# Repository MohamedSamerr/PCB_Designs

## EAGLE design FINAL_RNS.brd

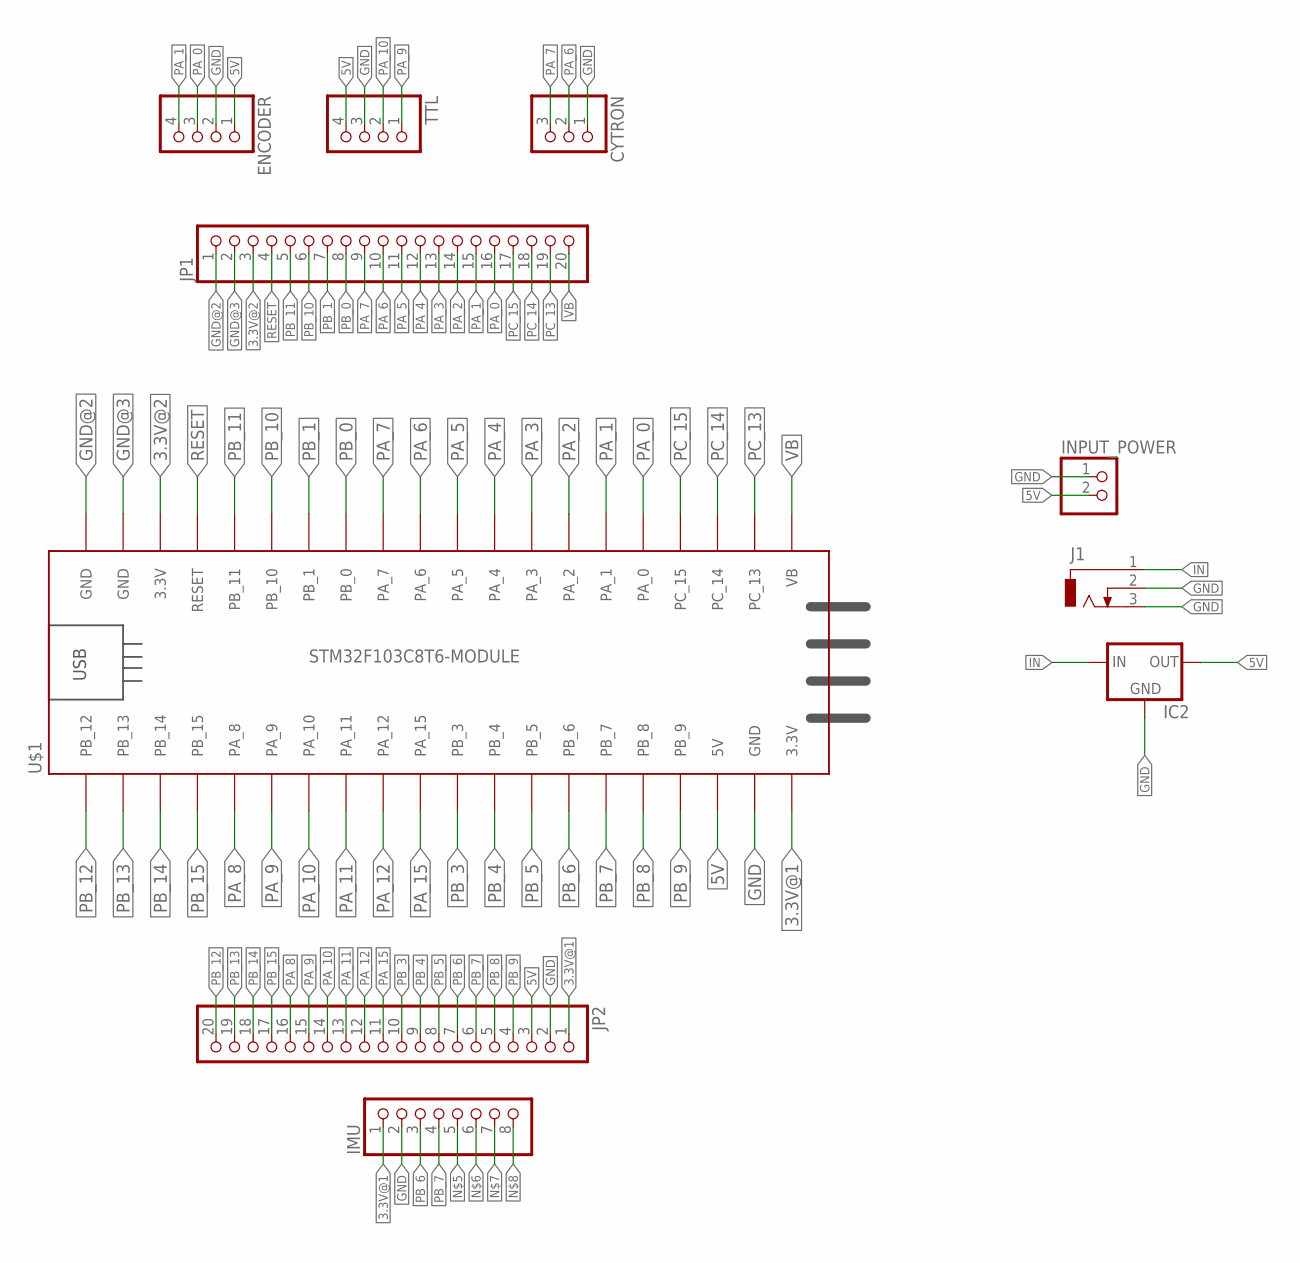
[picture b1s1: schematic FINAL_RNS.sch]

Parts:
CYTRON: PINHD-3_DATA; 1X03_DATA
ENCODER: PINHD-4_DATA; 1X04_DATA
IC2: 78XXS
IMU: PINHD-1X8; 1X08
INPUT_POWER: PINHD-2_DATA; 1X02_DATA
J1: CON_JACK; DCJ0303
JP1, JP2: PINHD-1X20; 1X20
TTL: PINHD-4_DATA; 1X04_DATA
U$1: STM32F103C8T6-MODULE

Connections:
3.3V@1: IMU.1, JP2.1, U$1.3.3V_1 (3.3V)
3.3V@2: JP1.3, U$1.3.3V_2 (3.3V)
5V: ENCODER.1, IC2.OUT, INPUT_POWER.2, JP2.3, TTL.4, U$1.5V
GND: CYTRON.1, ENCODER.2, IC2.GND, IMU.2, INPUT_POWER.1, J1.2, J1.3, JP2.2, TTL.3, U$1.GND_1 (GND)
GND@2: JP1.1, U$1.GND_3 (GND)
GND@3: JP1.2, U$1.GND_2 (GND)
IN: IC2.IN, J1.1
PA_0: ENCODER.3, JP1.16, U$1.PA_0
PA_1: ENCODER.4, JP1.15, U$1.PA_1
PA_2: JP1.14, U$1.PA_2
PA_3: JP1.13, U$1.PA_3
PA_4: JP1.12, U$1.PA_4
PA_5: JP1.11, U$1.PA_5
PA_6: CYTRON.2, JP1.10, U$1.PA_6
PA_7: CYTRON.3, JP1.9, U$1.PA_7
PA_8: JP2.16, U$1.PA_8
PA_9: JP2.15, TTL.1, U$1.PA_9
PA_10: JP2.14, TTL.2, U$1.PA_10
PA_11: JP2.13, U$1.PA_11
PA_12: JP2.12, U$1.PA_12
PA_15: JP2.11, U$1.PA_15
PB_0: JP1.8, U$1.PB_0
PB_1: JP1.7, U$1.PB_1
PB_3: JP2.10, U$1.PB_3
PB_4: JP2.9, U$1.PB_4
PB_5: JP2.8, U$1.PB_5
PB_6: IMU.3, JP2.7, U$1.PB_6
PB_7: IMU.4, JP2.6, U$1.PB_7
PB_8: JP2.5, U$1.PB_8
PB_9: JP2.4, U$1.PB_9
PB_10: JP1.6, U$1.PB_10
PB_11: JP1.5, U$1.PB_11
PB_12: JP2.20, U$1.PB_12
PB_13: JP2.19, U$1.PB_13
PB_14: JP2.18, U$1.PB_14
PB_15: JP2.17, U$1.PB_15
PC_13: JP1.19, U$1.PC_13
PC_14: JP1.18, U$1.PC_14
PC_15: JP1.17, U$1.PC_15
RESET: JP1.4, U$1.RESET
VB: JP1.20, U$1.VB

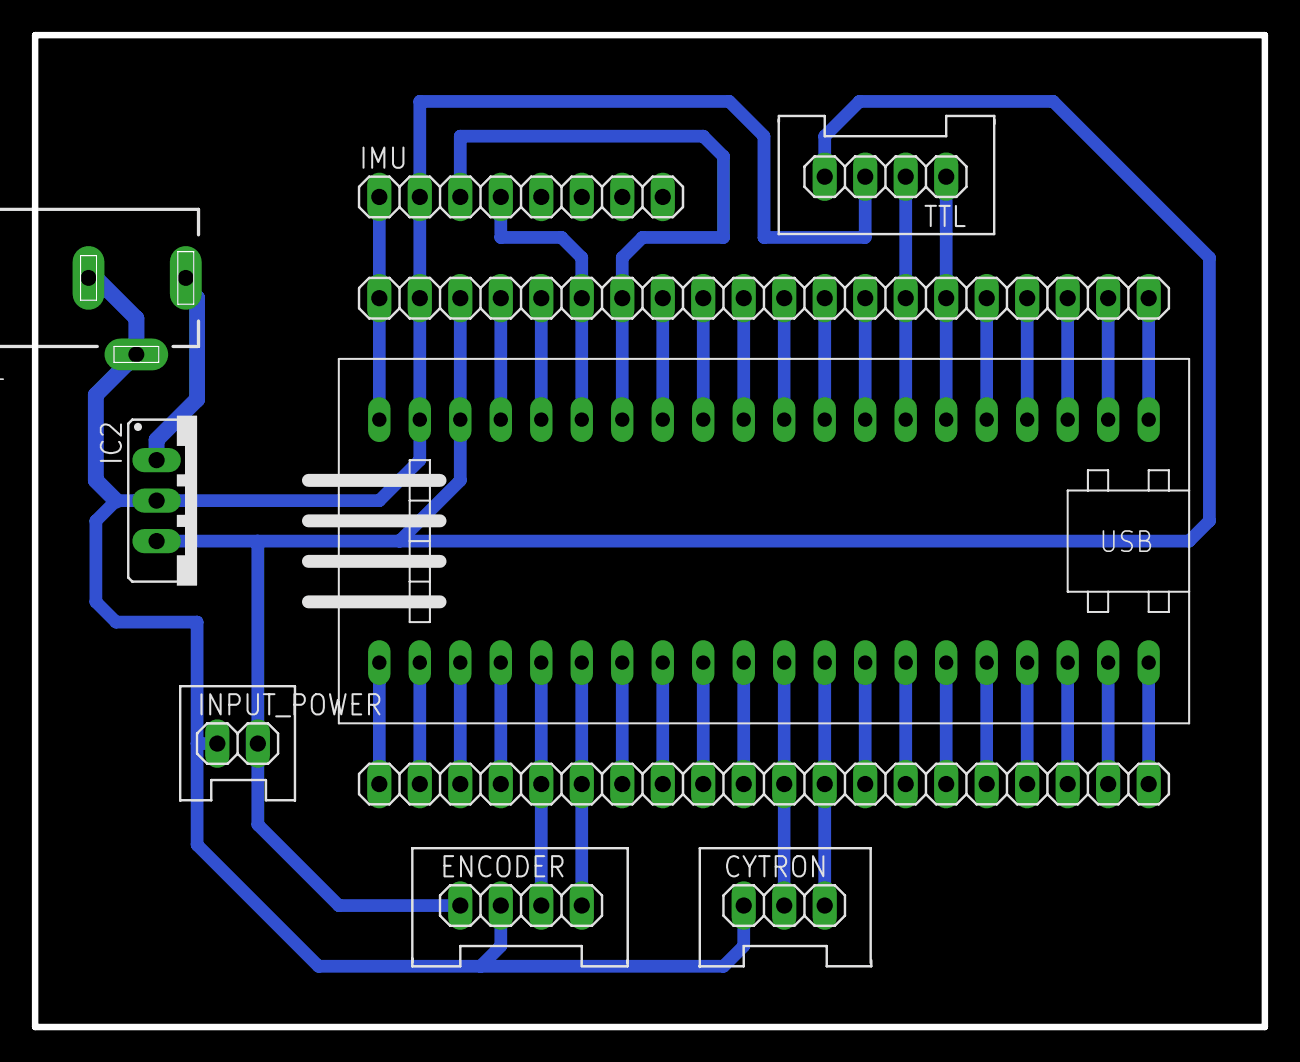
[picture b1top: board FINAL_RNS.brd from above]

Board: 2 copper layers, 77.1 x 62.2 mm, 10 parts (0 on the bottom side), 41 nets.

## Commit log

2022-10-10 added shematic and pcb design
2022-10-13 added new design
